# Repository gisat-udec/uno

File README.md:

## Primer CANSAT

Presentado durante la **Feria de Innovación de Ingeniería** el 16/12/2022

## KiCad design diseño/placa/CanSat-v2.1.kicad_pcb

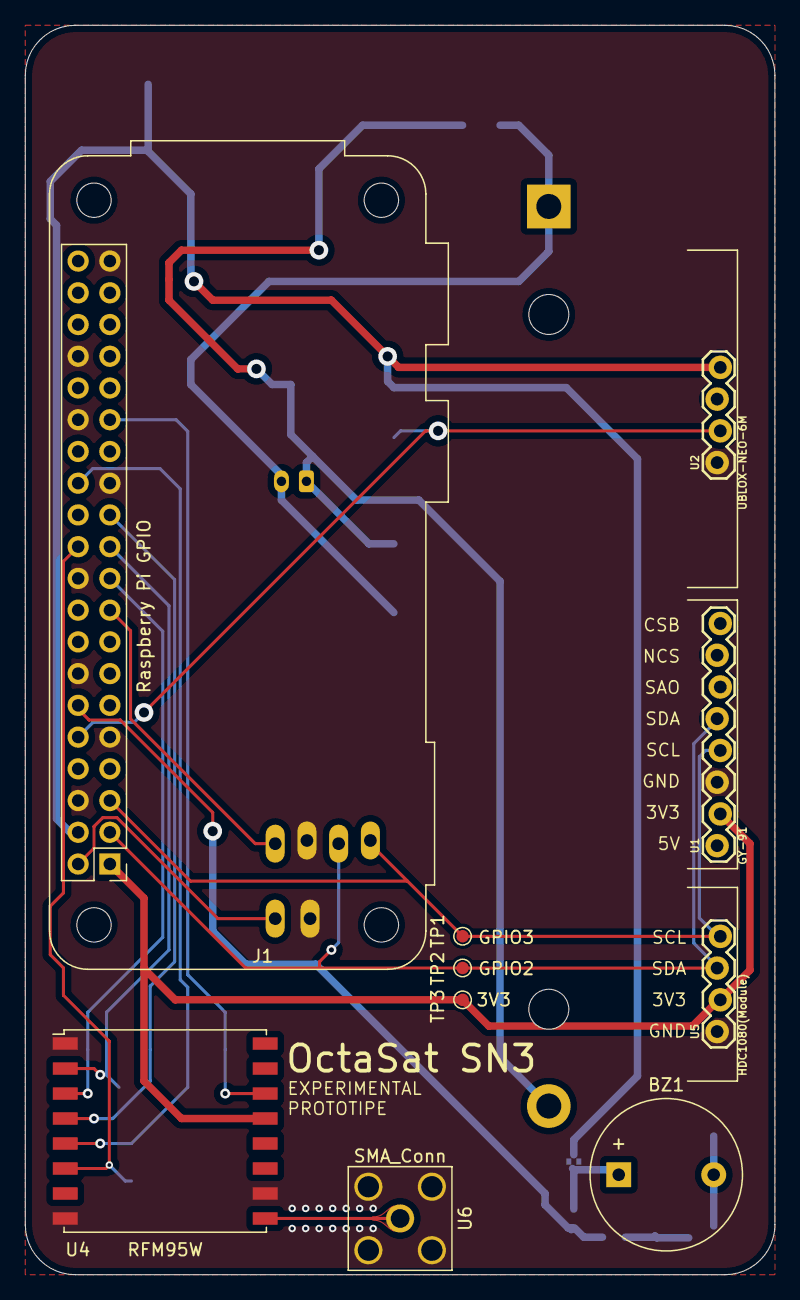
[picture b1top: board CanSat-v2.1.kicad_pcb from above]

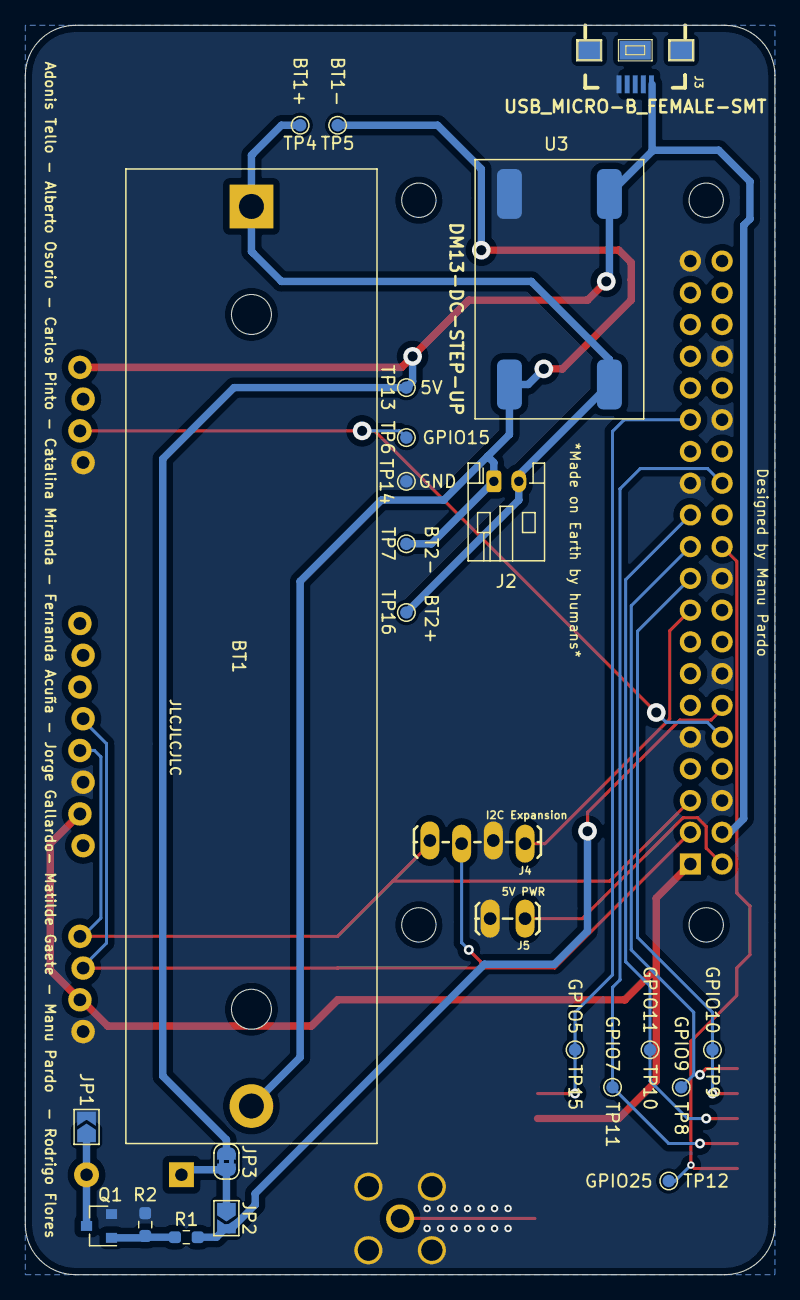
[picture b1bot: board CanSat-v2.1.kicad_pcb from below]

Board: 2 copper layers, 60.0 x 100.0 mm, 35 parts (26 on the bottom side), 19 nets.

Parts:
BT1: 3.7v 1S Li-ion; BatteryHolder_MPD_BH-18650-PC2
BZ1: Buzzer; Buzzer_12x9.5RM7.6
J1: Raspberry Pi GPIO; Raspberry_Pi_Zero_Socketed_THT_FaceDown_MountingHoles
J2: Secondary Power Input; JST_PH_S2B-PH-K_1x02_P2.00mm_Horizontal
J3: USB_MICRO-B_FEMALE-SMT; USB-B-MICRO-SMD
J4: I2C Expansion; 1X04_LOCK_LONGPADS
J5: 5V PWR; 1X02_LOCK_LONGPADS
JP1, JP2: Jumper_NO_Small; SolderJumper-2_P1.3mm_Open_TrianglePad1.0x1.5mm
JP3: Jumper_NC_Small; SolderJumper-2_P1.3mm_Bridged2Bar_RoundedPad1.0x1.5mm
Q1: DMG3404L; SOT-23
R1, R2: R_Small; R_0603_1608Metric_Pad0.98x0.95mm_HandSolder
TP1: GPIO3; TestPoint_Pad_D1.0mm
TP2: GPIO2; TestPoint_Pad_D1.0mm
TP3: 3V3; TestPoint_Pad_D1.0mm
TP4: BT1+; TestPoint_Pad_D1.0mm
TP5: BT1-; TestPoint_Pad_D1.0mm
TP6: GPIO15; TestPoint_Pad_D1.0mm
TP7: BT2-; TestPoint_Pad_D1.0mm
TP8: GPIO9; TestPoint_Pad_D1.0mm
TP9: GPIO10; TestPoint_Pad_D1.0mm
TP10: GPIO11; TestPoint_Pad_D1.0mm
TP11: GPIO7; TestPoint_Pad_D1.0mm
TP12: GPIO25; TestPoint_Pad_D1.0mm
TP13: 5V; TestPoint_Pad_D1.0mm
TP14: GND; TestPoint_Pad_D1.0mm
TP15: GPIO5; TestPoint_Pad_D1.0mm
TP16: BT2+; TestPoint_Pad_D1.0mm
U1: GY-91; 1X08_LOCK
U2: UBLOX-NEO-6M; 1X04_LOCK
U3: DM13-DC-STEP-UP; DM13
U4: RFM95W; HOPERF_RFM9XW_SMD
U5: HDC1080(Module); 1X04_LOCK
U6: SMA_Conn; SMA_Amphenol_132203-12_Horizontal

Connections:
3V3: J1.1, J1.17, J4.1, TP3.1, U1.2, U4.13, U5.2
5V: J1.2, J1.4, J3.VBUS, J5.1, JP3.1, TP13.1, U2.4, U3.3
BT1+: BT1.1, J2.2, TP4.1, TP16.1, U3.1
BT1-: BT1.2, J2.1, TP5.1, TP7.1, U3.2
GND: J1.6, J1.9, J1.14, J1.20, J1.25, J1.30, J1.34, J1.39, J3.GND, J4.2, J5.2, JP1.2, Q1.2, R2.1, TP14.1, U1.3, U2.1, U3.4, U4.1, U4.8, U4.10, U5.1, U6.2
GPIO2: J1.3, J4.3, TP2.1, U1.5, U5.3
GPIO3: J1.5, J4.4, TP1.1, U1.4, U5.4
GPIO5: J1.29, TP15.1, U4.14
GPIO7: J1.26, TP11.1, U4.5
GPIO15: J1.10, TP6.1, U2.2
GPIO18: J1.12, JP2.2, R1.2
GPIO25: J1.22, TP12.1, U4.6
MISO: J1.21, TP8.1, U4.2
MOSI: J1.19, TP9.1, U4.3
unnamed: BZ1.1, JP2.1, JP3.2
unnamed: BZ1.2, JP1.1, Q1.3
unnamed: Q1.1, R1.1, R2.2
RFM_ANT: U4.9, U6.1
SCLK: J1.23, TP10.1, U4.4

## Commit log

2022-09-02 inicio
2022-09-02 prueba commit de jupyter lab
2022-09-02 primeros cambios
2022-09-02 hdc1080
2022-09-02 más modulos
2022-09-02 hardware cansat
2022-09-02 save
2022-09-02 diagramas
2022-09-03 placa
2022-09-03 hardware extra
2022-09-03 copy paste
2022-11-17 hola
2022-12-14 carpetas
2022-12-15 inicios codigo
2022-12-15 print de todos los sensores
2022-12-16 dios santo
2022-12-16 increible
2022-12-16 sin timepo
2022-12-16 ya esta weno
2022-12-16 fix up
2022-12-16 orden
2023-04-12 imagenes
